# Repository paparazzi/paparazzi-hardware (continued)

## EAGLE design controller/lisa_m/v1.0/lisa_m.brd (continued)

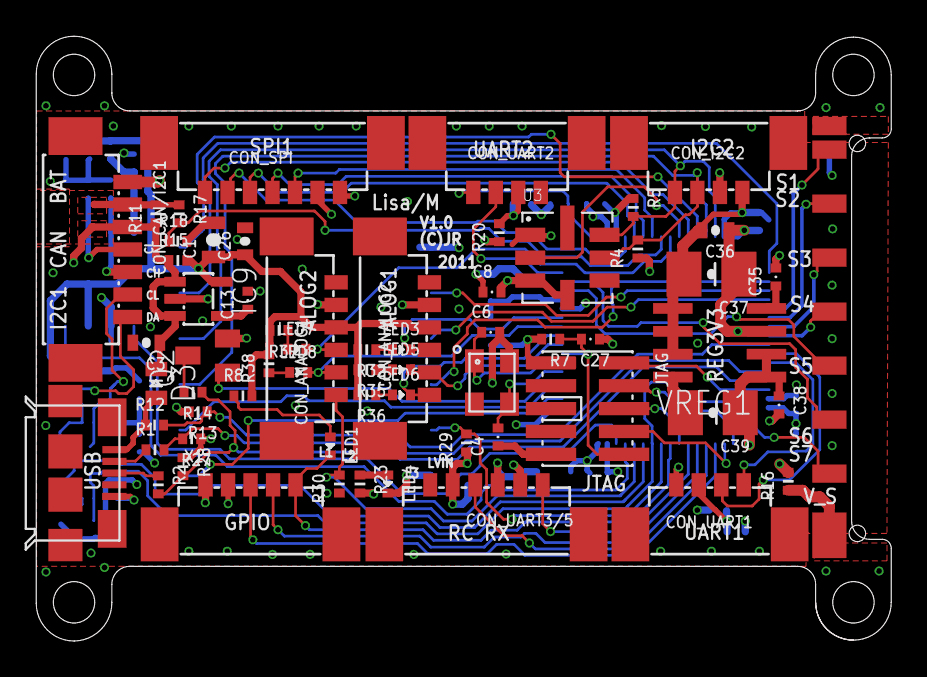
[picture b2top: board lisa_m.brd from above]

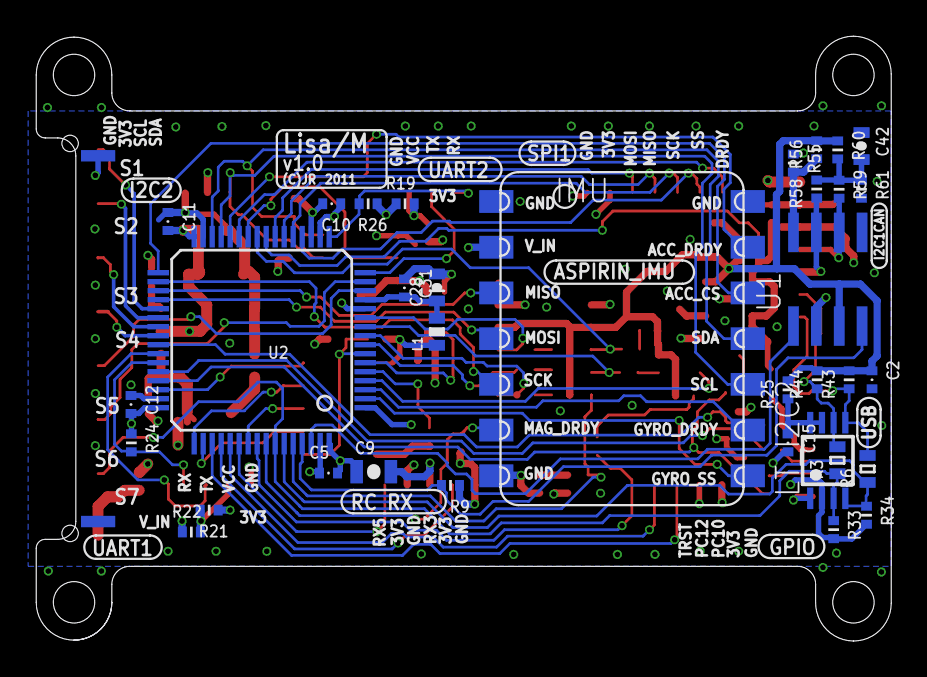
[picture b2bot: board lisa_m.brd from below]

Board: 4 copper layers, 47.5 x 33.6 mm, 97 parts (34 on the bottom side), 82 nets.

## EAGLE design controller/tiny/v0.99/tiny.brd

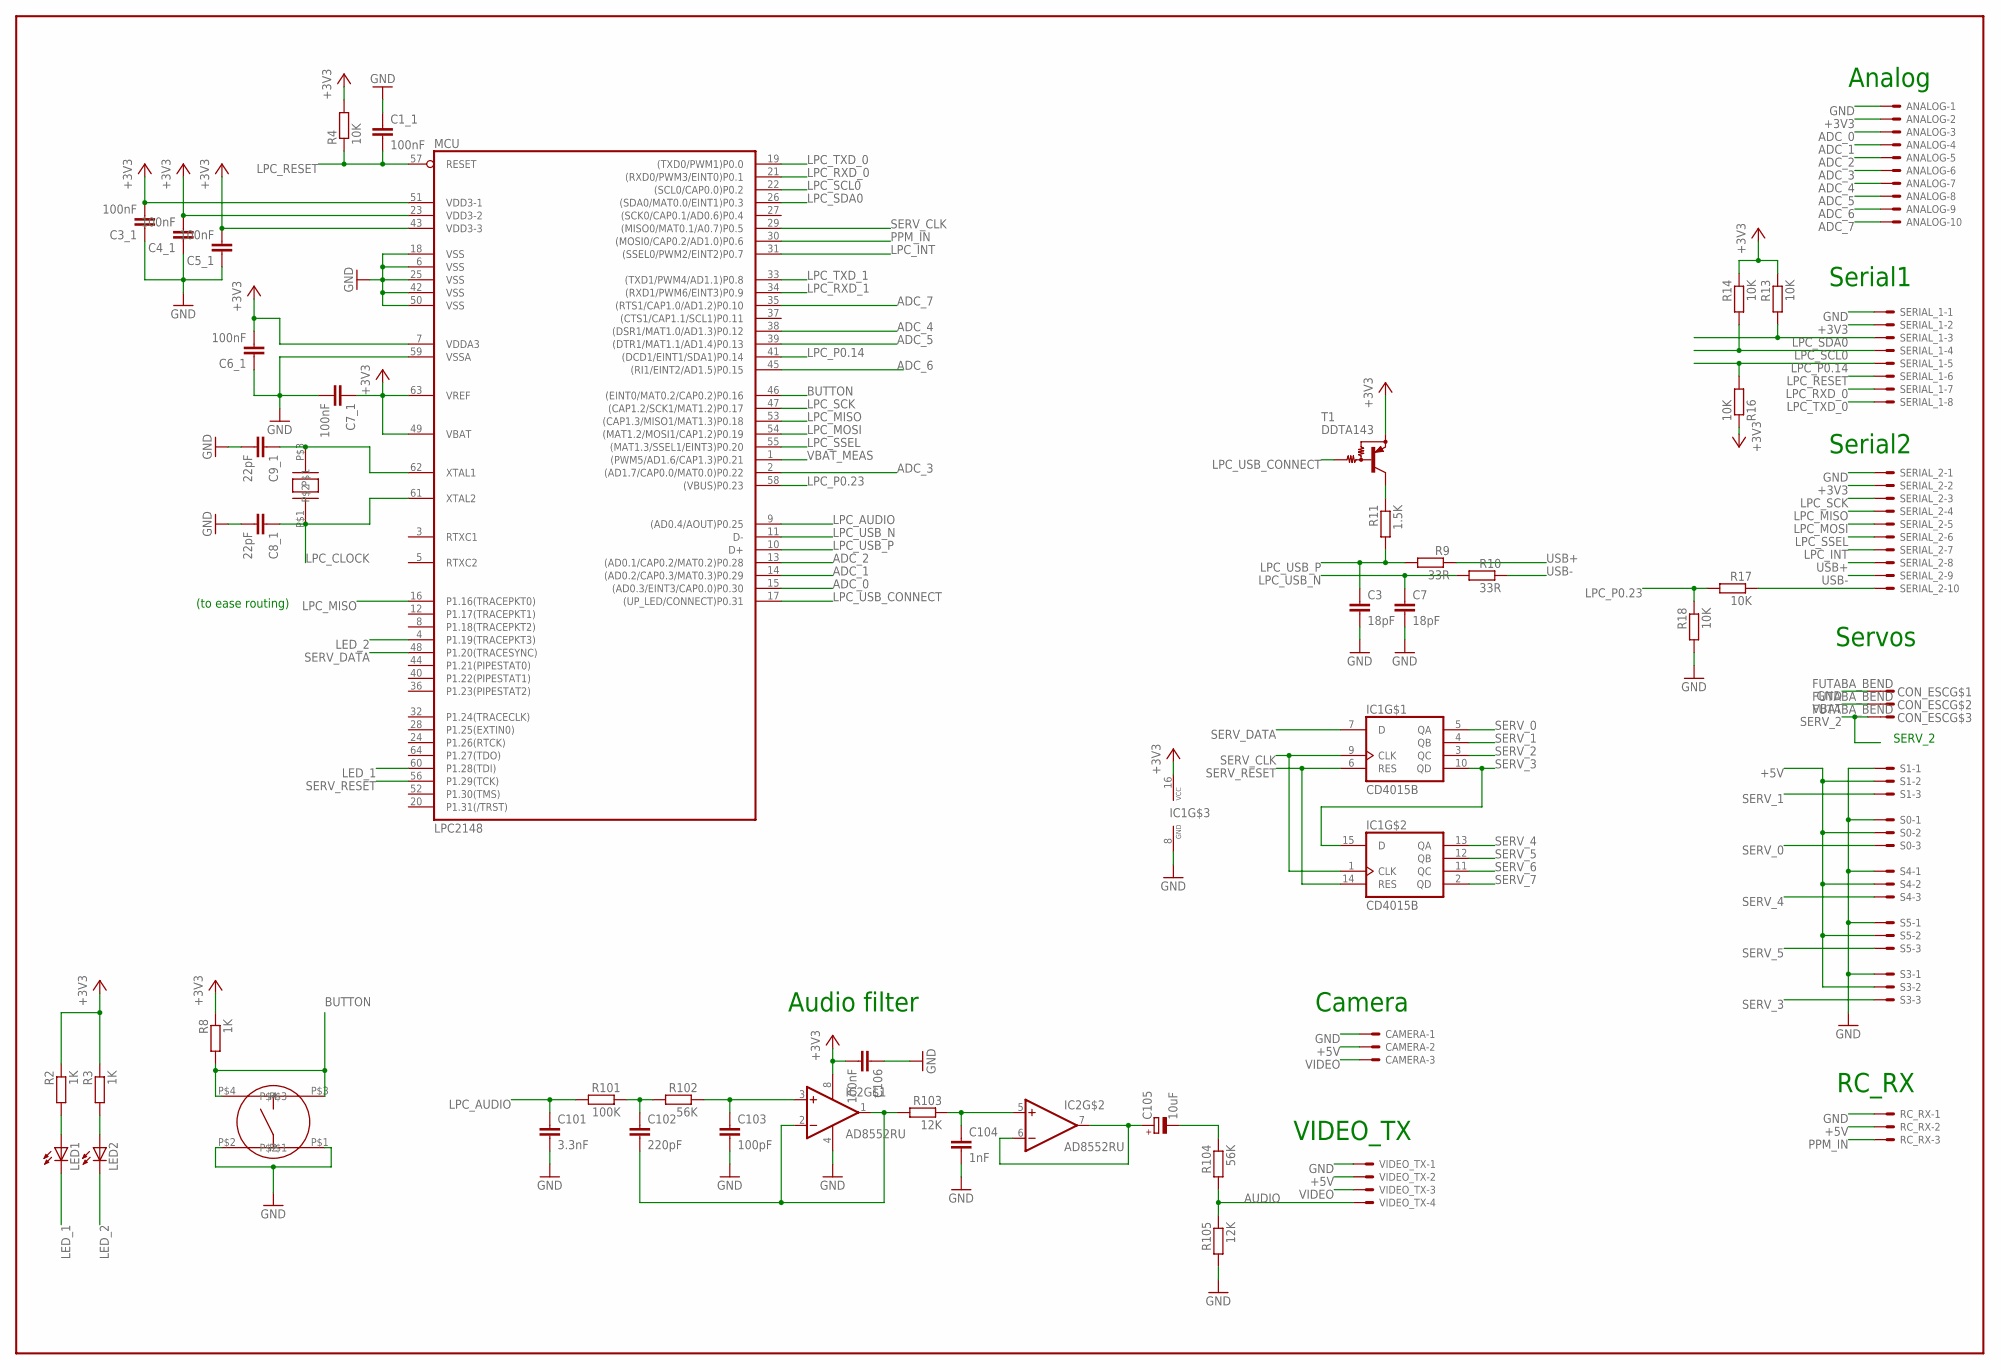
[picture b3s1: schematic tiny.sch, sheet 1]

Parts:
ANALOG: 53047-10
C1_1, C3_1, C4_1, C5_1, C6_1, C7_1, C106: 100nF; C0402K
C3, C7: 18pF; C0402K
C8_1, C9_1: 22pF; C0402K
C101: 3.3nF; C0402K
C102: 220pF; C0402K
C103: 100pF; C0402K
C104: 1nF; C0402K
C105: 10uF; A/3216-18R
CAMERA: 53047-03
CON_ESC: FUTABA_BEND; FUTABA_BENDED
IC1: CD4015B; TSSOP16
IC2: AD8552RU; TSSOP8
LED1, LED2: LEDCHIP-LED0805; CHIP-LED0805
MCU: LPC2148; SQFP-S-10X10-64
Q1: 12MHz; CTS_CRYSTAL
R2, R3, R8: 1K; R1005
R4, R13, R14, R16, R17, R18: 10K; R1005
R9, R10: 33R; R1005
R11: 1.5K; R1005
R101: 100K; R1005
R102, R104: 56K; R1005
R103, R105: 12K; R1005
RC_RX: 53047-03
S0, S1, S3, S4, S5: 53047-03
SERIAL_1: 53047-08
SERIAL_2: 53047-10
SW1: B3S
T1: DDTA143; SC59-BEC
VIDEO_TX: 53047-04

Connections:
+3V3: ANALOG.2, C3_1.2, C4_1.2, C5_1.2, C6_1.2, C7_1.1, C106.2, IC1.16 (VCC), IC2.8 (V+), MCU.7 (VDDA3), MCU.23 (VDD3-2), MCU.43 (VDD3-3), MCU.49 (VBAT), MCU.51 (VDD3-1), MCU.63 (VREF), R2.1, R3.1, R4.2, R8.1, R13.1, R14.1, R16.1, SERIAL_1.2, SERIAL_2.2, T1.E; also elsewhere on the board
+5V: CAMERA.2, RC_RX.2, S0.2, S1.2, S3.2, S4.2, S5.2, VIDEO_TX.2; also elsewhere on the board
ADC_0: ANALOG.3, MCU.15 ((AD0.3/EINT3/CAP0.0)P0.30)
ADC_1: ANALOG.4, MCU.14 ((AD0.2/CAP0.3/MAT0.3)P0.29)
ADC_2: ANALOG.5, MCU.13 ((AD0.1/CAP0.2/MAT0.2)P0.28)
ADC_3: ANALOG.6, MCU.2 ((AD1.7/CAP0.0/MAT0.0)P0.22)
ADC_4: ANALOG.7, MCU.38 ((DSR1/MAT1.0/AD1.3)P0.12)
ADC_5: ANALOG.8, MCU.39 ((DTR1/MAT1.1/AD1.4)P0.13)
ADC_6: ANALOG.9, MCU.45 ((RI1/EINT2/AD1.5)P0.15)
ADC_7: ANALOG.10, MCU.35 ((RTS1/CAP1.0/AD1.2)P0.10)
AUDIO: R104.2, R105.1, VIDEO_TX.4
BUTTON: MCU.46 ((EINT0/MAT0.2/CAP0.2)P0.16), R8.2, SW1.P$3, SW1.P$4
GND: ANALOG.1, C1_1.1, C3.2, C3_1.1, C4_1.1, C5_1.1, C6_1.1, C7.2, C7_1.2, C8_1.2, C9_1.2, C101.2, C103.2, C104.2, C106.1, CAMERA.1, CON_ESC.1, IC1.8 (GND), IC2.4 (V-), MCU.6 (VSS), MCU.18 (VSS), MCU.25 (VSS), MCU.42 (VSS), MCU.50 (VSS), MCU.59 (VSSA), R18.2, R105.2, RC_RX.1, S0.1, S1.1, S3.1, S4.1, S5.1, SERIAL_1.1, SERIAL_2.1, SW1.P$1, SW1.P$2, VIDEO_TX.1; also elsewhere on the board
LED_1: LED1.C, MCU.60 (P1.28(TDI))
LED_2: LED2.C, MCU.4 (P1.19(TRACEPKT3))
LPC_AUDIO: C101.1, MCU.9 ((AD0.4/AOUT)P0.25), R101.2
LPC_CLOCK: C8_1.1, MCU.61 (XTAL2), Q1.P$1
LPC_INT: MCU.31 ((SSEL0/PWM2/EINT2)P0.7), SERIAL_2.7
LPC_MISO: MCU.16 (P1.16(TRACEPKT0)), MCU.53 ((CAP1.3/MISO1/MAT1.3)P0.18), SERIAL_2.4
LPC_MOSI: MCU.54 ((MAT1.2/MOSI1/CAP1.2)P0.19), SERIAL_2.5
LPC_P0.14: MCU.41 ((DCD1/EINT1/SDA1)P0.14), R16.2, SERIAL_1.5
LPC_P0.23: MCU.58 ((VBUS)P0.23), R17.2, R18.1
LPC_RESET: C1_1.2, MCU.57 (RESET), R4.1, SERIAL_1.6
LPC_RXD_0: MCU.21 ((RXD0/PWM3/EINT0)P0.1), SERIAL_1.7
LPC_RXD_1: MCU.34 ((RXD1/PWM6/EINT3)P0.9); also elsewhere on the board
LPC_SCK: MCU.47 ((CAP1.2/SCK1/MAT1.2)P0.17), SERIAL_2.3
LPC_SCL0: MCU.22 ((SCL0/CAP0.0)P0.2), R14.2, SERIAL_1.4
LPC_SDA0: MCU.26 ((SDA0/MAT0.0/EINT1)P0.3), R13.2, SERIAL_1.3
LPC_SSEL: MCU.55 ((MAT1.3/SSEL1/EINT3)P0.20), SERIAL_2.6
LPC_TXD_0: MCU.19 ((TXD0/PWM1)P0.0), SERIAL_1.8
LPC_TXD_1: MCU.33 ((TXD1/PWM4/AD1.1)P0.8); also elsewhere on the board
LPC_USB_CONNECT: MCU.17 ((UP_LED/CONNECT)P0.31), T1.B
LPC_USB_N: C7.1, MCU.11 (D-), R10.2
LPC_USB_P: C3.1, MCU.10 (D+), R9.2, R11.2
unnamed: R17.1, SERIAL_2.10
unnamed: C9_1.1, MCU.62 (XTAL1), Q1.P$3
unnamed: R11.1, T1.C
unnamed: C105.+, IC2.6 (-IN), IC2.7 (OUT)
unnamed: C102.2, IC2.1 (OUT), IC2.2 (-IN), R103.2
unnamed: C102.1, R101.1, R102.2
unnamed: C103.1, IC2.3 (+IN), R102.1
unnamed: C105.-, R104.1
unnamed: C104.1, IC2.5 (+IN), R103.1
unnamed: LED1.A, R2.2
unnamed: LED2.A, R3.2
PPM_IN: MCU.30 ((MOSI0/CAP0.2/AD1.0)P0.6), RC_RX.3
SERV_0: IC1.5 (QA), S0.3
SERV_1: IC1.4 (QB), S1.3
SERV_2: CON_ESC.3, IC1.3 (QC)
SERV_3: IC1.10 (QD), IC1.15 (D), S3.3
SERV_4: IC1.13 (QA), S4.3
SERV_5: IC1.12 (QB), S5.3
SERV_6: IC1.11 (QC)
SERV_7: IC1.2 (QD)
SERV_CLK: IC1.1 (CLK), IC1.9 (CLK), MCU.29 ((MISO0/MAT0.1/A0.7)P0.5)
SERV_DATA: IC1.7 (D), MCU.48 (P1.20(TRACESYNC))
SERV_RESET: IC1.6 (RES), IC1.14 (RES), MCU.56 (P1.29(TCK))
USB+: R9.1, SERIAL_2.8
USB-: R10.1, SERIAL_2.9
VBAT: CON_ESC.2; also elsewhere on the board
VBAT_MEAS: MCU.1 ((PWM5/AD1.6/CAP1.3)P0.21); also elsewhere on the board
VIDEO: CAMERA.3, VIDEO_TX.3

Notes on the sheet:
Servos
Serial2
VIDEO_TX
Analog
Camera
RC_RX
SERV_2
(to ease routing)
Serial1
Audio filter

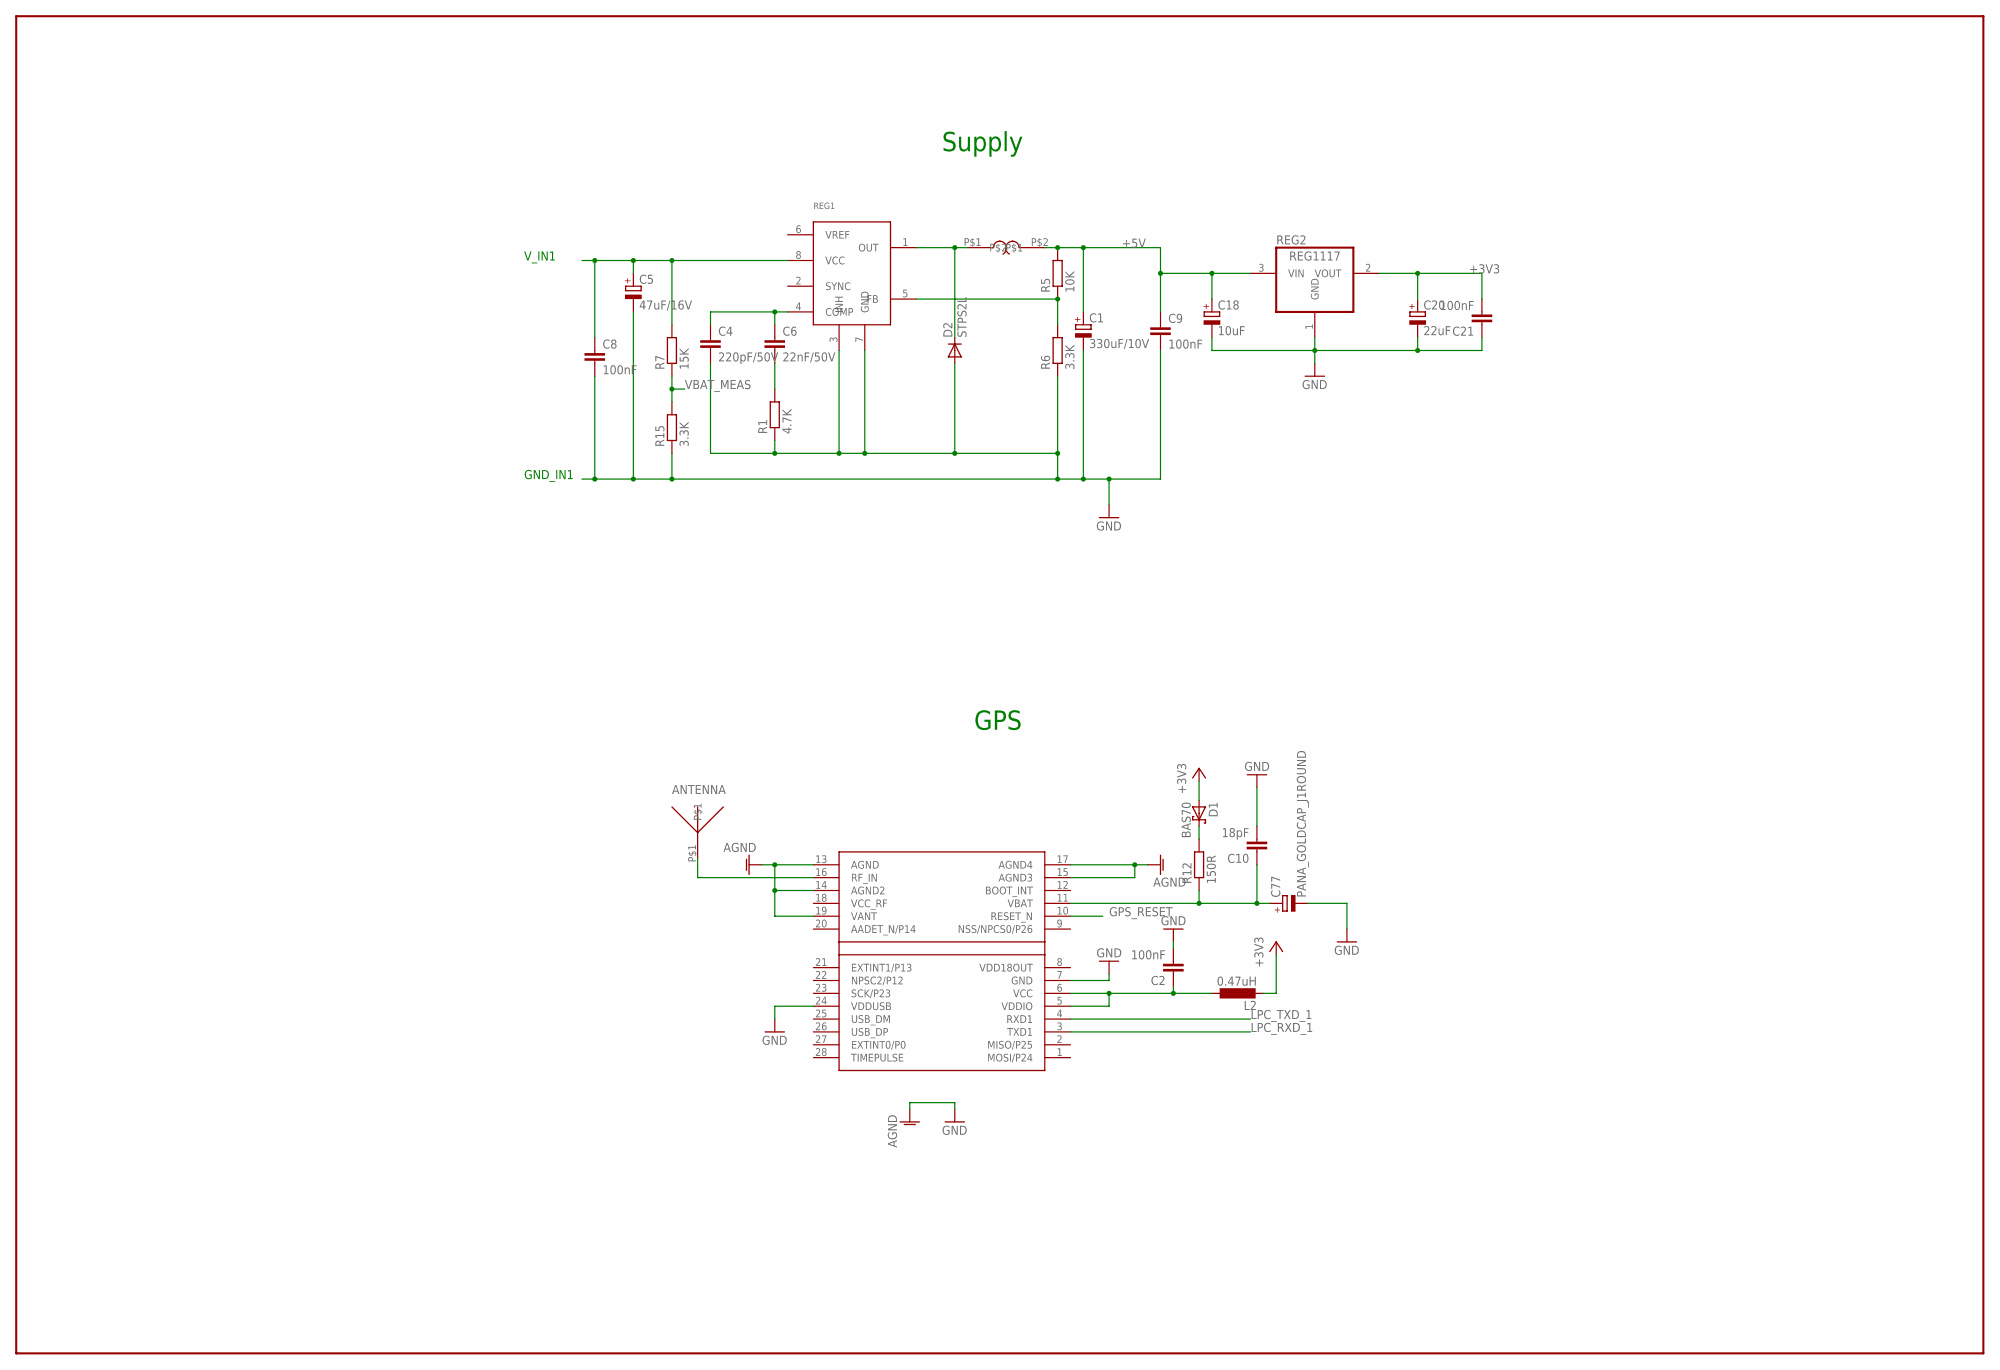
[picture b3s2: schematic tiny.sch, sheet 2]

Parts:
ANTENNA: GPS_ANT_13
C1: 330uF/10V; D/7343-31R
C2: 100nF; C0402K
C4: 220pF/50V; C1206K
C5: 47uF/16V; D/7343-31R
C6: 22nF/50V; C1206K
C8, C9, C21: 100nF; C0603
C10: 18pF; C0402K
C18: 10uF; A/3216-18R
C20: 22uF; B/3528-21R
C77: PANA_GOLDCAP_J1ROUND; PANA_J1_BIS
D1: BAS70; SOT23
D2: STPS2L; SMA
GPS: LEA-4P; LEA-LA
L1: 15uH; WE_PD
L2: 0.47uH; L2012C
R1: 4.7K; R1005
R5: 10K; R1005
R6, R15: 3.3K; R1005
R7: 15K; R1005
R12: 150R; R1005
REG1: L5973D; SO08
REG2: REG1117; SOT223

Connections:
+3V3: C20.+, C21.2, D1.1 (A), L2.2, REG2.2 (VOUT); also elsewhere on the board
+5V: C1.+, C9.1, C18.+, L1.P$2, R5.2, REG2.3 (VIN); also elsewhere on the board
GND: C1.-, C2.2, C4.2, C5.-, C8.2, C9.2, C10.2, C18.-, C20.-, C21.1, C77.MINUS (-), D2.P$1 (A), GPS.7 (GND), GPS.13 (AGND), GPS.14 (AGND2), GPS.15 (AGND3), GPS.17 (AGND4), GPS.19 (VANT), GPS.24 (VDDUSB), R1.1, R6.1, R15.1, REG1.3 (INH), REG1.7 (GND), REG2.1 (GND); also elsewhere on the board
GPS_RESET: GPS.10 (RESET_N)
LPC_RXD_1: GPS.3 (TXD1); also elsewhere on the board
LPC_TXD_1: GPS.4 (RXD1); also elsewhere on the board
unnamed: C2.1, GPS.5 (VDDIO), GPS.6 (VCC), L2.1
unnamed: ANTENNA.P$1, GPS.16 (RF_IN)
unnamed: C4.1, C6.1, REG1.4 (COMP)
unnamed: C6.2, R1.2
unnamed: D2.P$2 (C), L1.P$1, REG1.1 (OUT)
unnamed: R5.1, R6.2, REG1.5 (FB)
unnamed: C10.1, C77.PLUS (+), GPS.11 (VBAT), R12.1
unnamed: D1.3 (C), R12.2
VBAT: C5.+, C8.1, R7.2, REG1.8 (VCC); also elsewhere on the board
VBAT_MEAS: R7.1, R15.2; also elsewhere on the board
VCC_RF: GPS.18 (VCC_RF)
VDD18OUT: GPS.8 (VDD18OUT)

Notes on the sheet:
V_IN1
GND_IN1
Supply
GPS

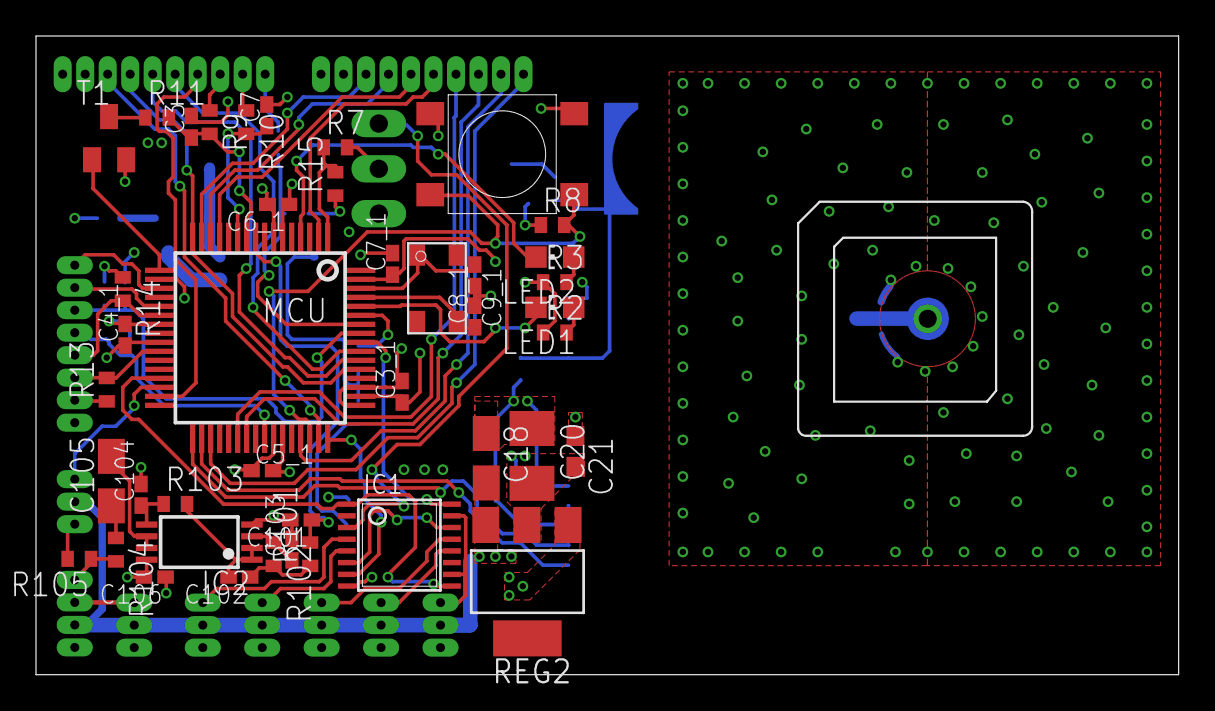
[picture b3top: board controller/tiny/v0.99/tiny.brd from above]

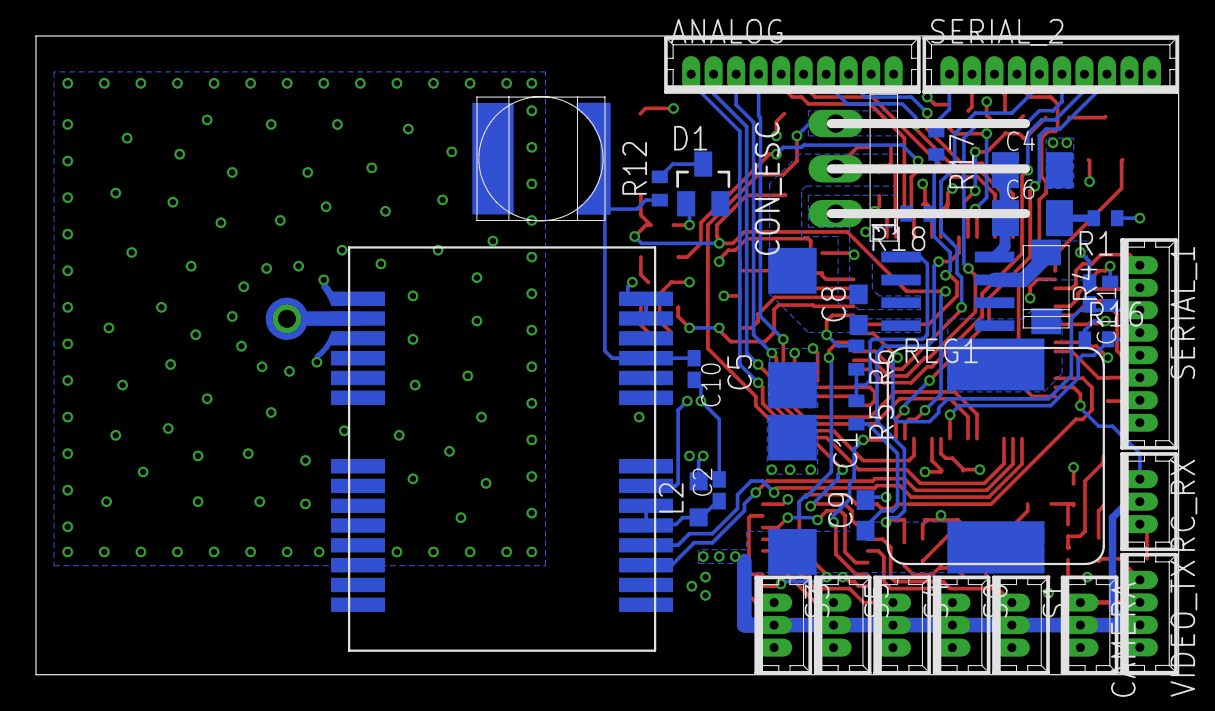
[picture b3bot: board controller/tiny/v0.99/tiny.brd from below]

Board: 4 copper layers, 63.5 x 35.5 mm, 79 parts (36 on the bottom side), 68 nets.

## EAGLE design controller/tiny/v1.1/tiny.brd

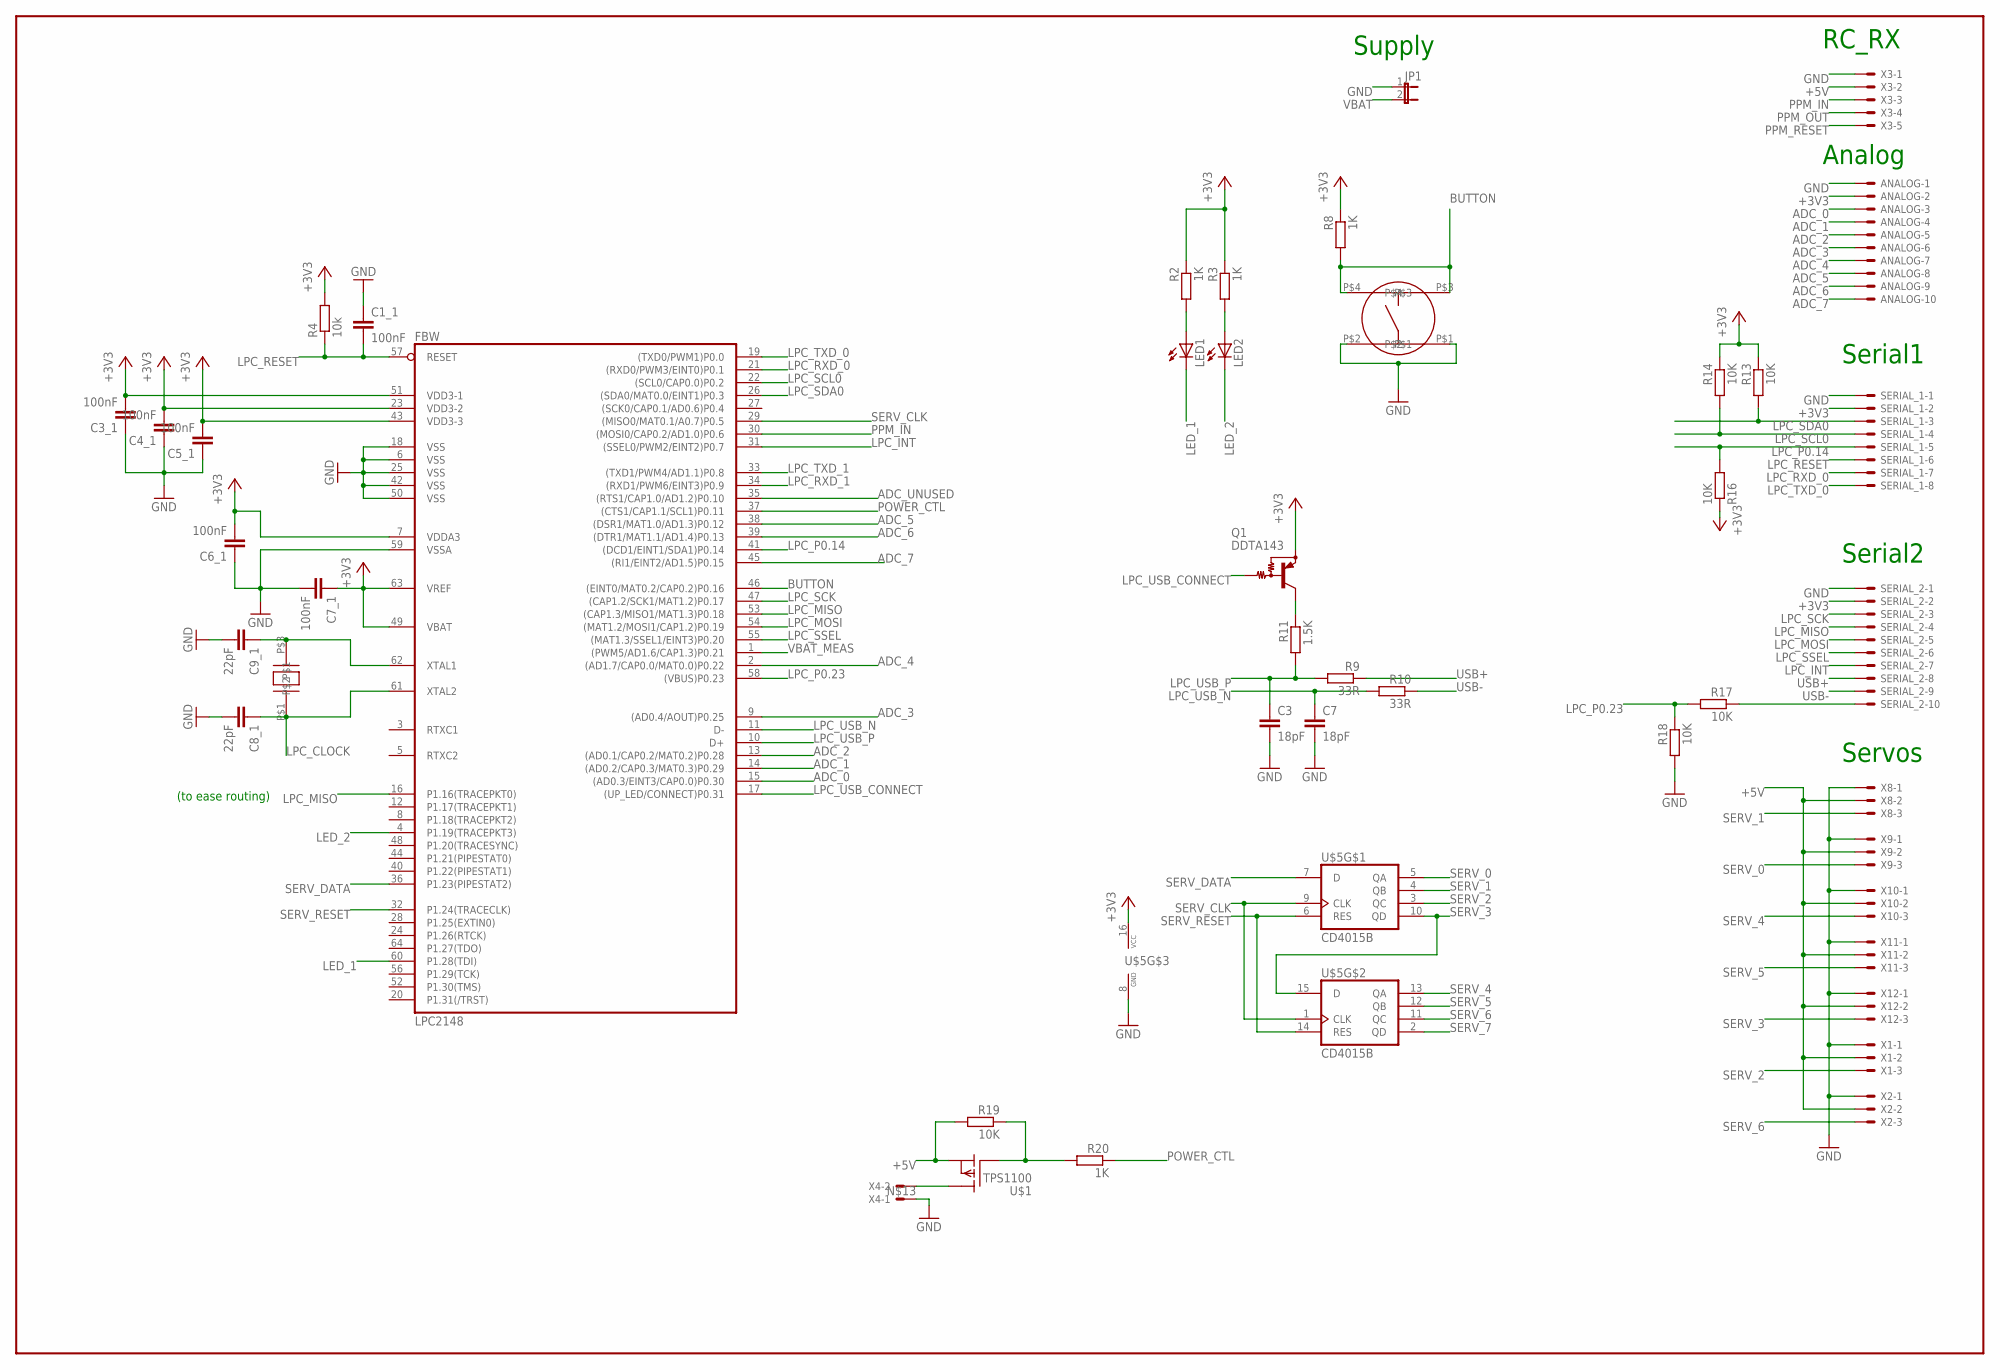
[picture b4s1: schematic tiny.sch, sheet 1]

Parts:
ANALOG: 53047-10
C1_1, C3_1, C4_1, C5_1, C6_1, C7_1: 100nF; C0402K
C3, C7: 18pF; C0402K
C8_1, C9_1: 22pF; C0402K
FBW: LPC2148; SQFP-S-10X10-64
JP1: JP1E; JP1
LED1, LED2: LEDCHIP-LED0805; CHIP-LED0805
Q1: DDTA143; SC59-BEC
R2, R3, R8, R20: 1K; R1005
R4: 10k; R1005
R9, R10: 33R; R1005
R11: 1.5K; R1005
R13, R14, R16, R17, R18, R19: 10K; R1005
SERIAL_1: 53047-08
SERIAL_2: 53047-10
SW1: B3S
U$1: TPS1100; SOIC8
U$5: CD4015B; TSSOP16
U$19: CRYSTAL_CTS; CTS_CRYSTAL
X1, X2, X8, X9, X10, X11, X12: 53047-03
X3: 53047-05
X4: 53047-02

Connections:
+3V3: ANALOG.2, C3_1.2, C4_1.2, C5_1.2, C6_1.2, C7_1.1, FBW.7 (VDDA3), FBW.23 (VDD3-2), FBW.43 (VDD3-3), FBW.49 (VBAT), FBW.51 (VDD3-1), FBW.63 (VREF), Q1.E, R2.1, R3.1, R4.2, R8.1, R13.1, R14.1, R16.1, SERIAL_1.2, SERIAL_2.2, U$5.16 (VCC); also elsewhere on the board
+5V: R19.2, U$1.1 (S), X1.2, X2.2, X3.2, X8.2, X9.2, X10.2, X11.2, X12.2; also elsewhere on the board
ADC_0: ANALOG.3, FBW.15 ((AD0.3/EINT3/CAP0.0)P0.30)
ADC_1: ANALOG.4, FBW.14 ((AD0.2/CAP0.3/MAT0.3)P0.29)
ADC_2: ANALOG.5, FBW.13 ((AD0.1/CAP0.2/MAT0.2)P0.28)
ADC_3: ANALOG.6, FBW.9 ((AD0.4/AOUT)P0.25)
ADC_4: ANALOG.7, FBW.2 ((AD1.7/CAP0.0/MAT0.0)P0.22)
ADC_5: ANALOG.8, FBW.38 ((DSR1/MAT1.0/AD1.3)P0.12)
ADC_6: ANALOG.9, FBW.39 ((DTR1/MAT1.1/AD1.4)P0.13)
ADC_7: ANALOG.10, FBW.45 ((RI1/EINT2/AD1.5)P0.15)
ADC_UNUSED: FBW.35 ((RTS1/CAP1.0/AD1.2)P0.10)
BUTTON: FBW.46 ((EINT0/MAT0.2/CAP0.2)P0.16), R8.2, SW1.P$3, SW1.P$4
GND: ANALOG.1, C1_1.1, C3.2, C3_1.1, C4_1.1, C5_1.1, C6_1.1, C7.2, C7_1.2, C8_1.2, C9_1.2, FBW.6 (VSS), FBW.18 (VSS), FBW.25 (VSS), FBW.42 (VSS), FBW.50 (VSS), FBW.59 (VSSA), JP1.1, R18.2, SERIAL_1.1, SERIAL_2.1, SW1.P$1, SW1.P$2, U$5.8 (GND), X1.1, X2.1, X3.1, X4.1, X8.1, X9.1, X10.1, X11.1, X12.1; also elsewhere on the board
LED_1: FBW.60 (P1.28(TDI)), LED1.C
LED_2: FBW.4 (P1.19(TRACEPKT3)), LED2.C
LPC_CLOCK: C8_1.1, FBW.61 (XTAL2), U$19.P$1
LPC_INT: FBW.31 ((SSEL0/PWM2/EINT2)P0.7), SERIAL_2.7
LPC_MISO: FBW.16 (P1.16(TRACEPKT0)), FBW.53 ((CAP1.3/MISO1/MAT1.3)P0.18), SERIAL_2.4
LPC_MOSI: FBW.54 ((MAT1.2/MOSI1/CAP1.2)P0.19), SERIAL_2.5
LPC_P0.14: FBW.41 ((DCD1/EINT1/SDA1)P0.14), R16.2, SERIAL_1.5
LPC_P0.23: FBW.58 ((VBUS)P0.23), R17.2, R18.1
LPC_RESET: C1_1.2, FBW.57 (RESET), R4.1, SERIAL_1.6
LPC_RXD_0: FBW.21 ((RXD0/PWM3/EINT0)P0.1), SERIAL_1.7
LPC_RXD_1: FBW.34 ((RXD1/PWM6/EINT3)P0.9); also elsewhere on the board
LPC_SCK: FBW.47 ((CAP1.2/SCK1/MAT1.2)P0.17), SERIAL_2.3
LPC_SCL0: FBW.22 ((SCL0/CAP0.0)P0.2), R14.2, SERIAL_1.4
LPC_SDA0: FBW.26 ((SDA0/MAT0.0/EINT1)P0.3), R13.2, SERIAL_1.3
LPC_SSEL: FBW.55 ((MAT1.3/SSEL1/EINT3)P0.20), SERIAL_2.6
LPC_TXD_0: FBW.19 ((TXD0/PWM1)P0.0), SERIAL_1.8
LPC_TXD_1: FBW.33 ((TXD1/PWM4/AD1.1)P0.8); also elsewhere on the board
LPC_USB_CONNECT: FBW.17 ((UP_LED/CONNECT)P0.31), Q1.B
LPC_USB_N: C7.1, FBW.11 (D-), R10.2
LPC_USB_P: C3.1, FBW.10 (D+), R9.2, R11.2
unnamed: R17.1, SERIAL_2.10
unnamed: C9_1.1, FBW.62 (XTAL1), U$19.P$3
unnamed: Q1.C, R11.1
unnamed: R19.1, R20.2, U$1.4 (G)
unnamed: U$1.5 (D), X4.2
unnamed: LED1.A, R2.2
unnamed: LED2.A, R3.2
POWER_CTL: FBW.37 ((CTS1/CAP1.1/SCL1)P0.11), R20.1
PPM_IN: FBW.30 ((MOSI0/CAP0.2/AD1.0)P0.6), X3.3
PPM_OUT: X3.4
PPM_RESET: X3.5
SERV_0: U$5.5 (QA), X9.3
SERV_1: U$5.4 (QB), X8.3
SERV_2: U$5.3 (QC), X1.3
SERV_3: U$5.10 (QD), U$5.15 (D), X12.3
SERV_4: U$5.13 (QA), X10.3
SERV_5: U$5.12 (QB), X11.3
SERV_6: U$5.11 (QC), X2.3
SERV_7: U$5.2 (QD)
SERV_CLK: FBW.29 ((MISO0/MAT0.1/A0.7)P0.5), U$5.1 (CLK), U$5.9 (CLK)
SERV_DATA: FBW.36 (P1.23(PIPESTAT2)), U$5.7 (D)
SERV_RESET: FBW.32 (P1.24(TRACECLK)), U$5.6 (RES), U$5.14 (RES)
USB+: R9.1, SERIAL_2.8
USB-: R10.1, SERIAL_2.9
VBAT: JP1.2; also elsewhere on the board
VBAT_MEAS: FBW.1 ((PWM5/AD1.6/CAP1.3)P0.21); also elsewhere on the board

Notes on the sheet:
Servos
Serial1
Analog
RC_RX
(to ease routing)
Serial2
Supply

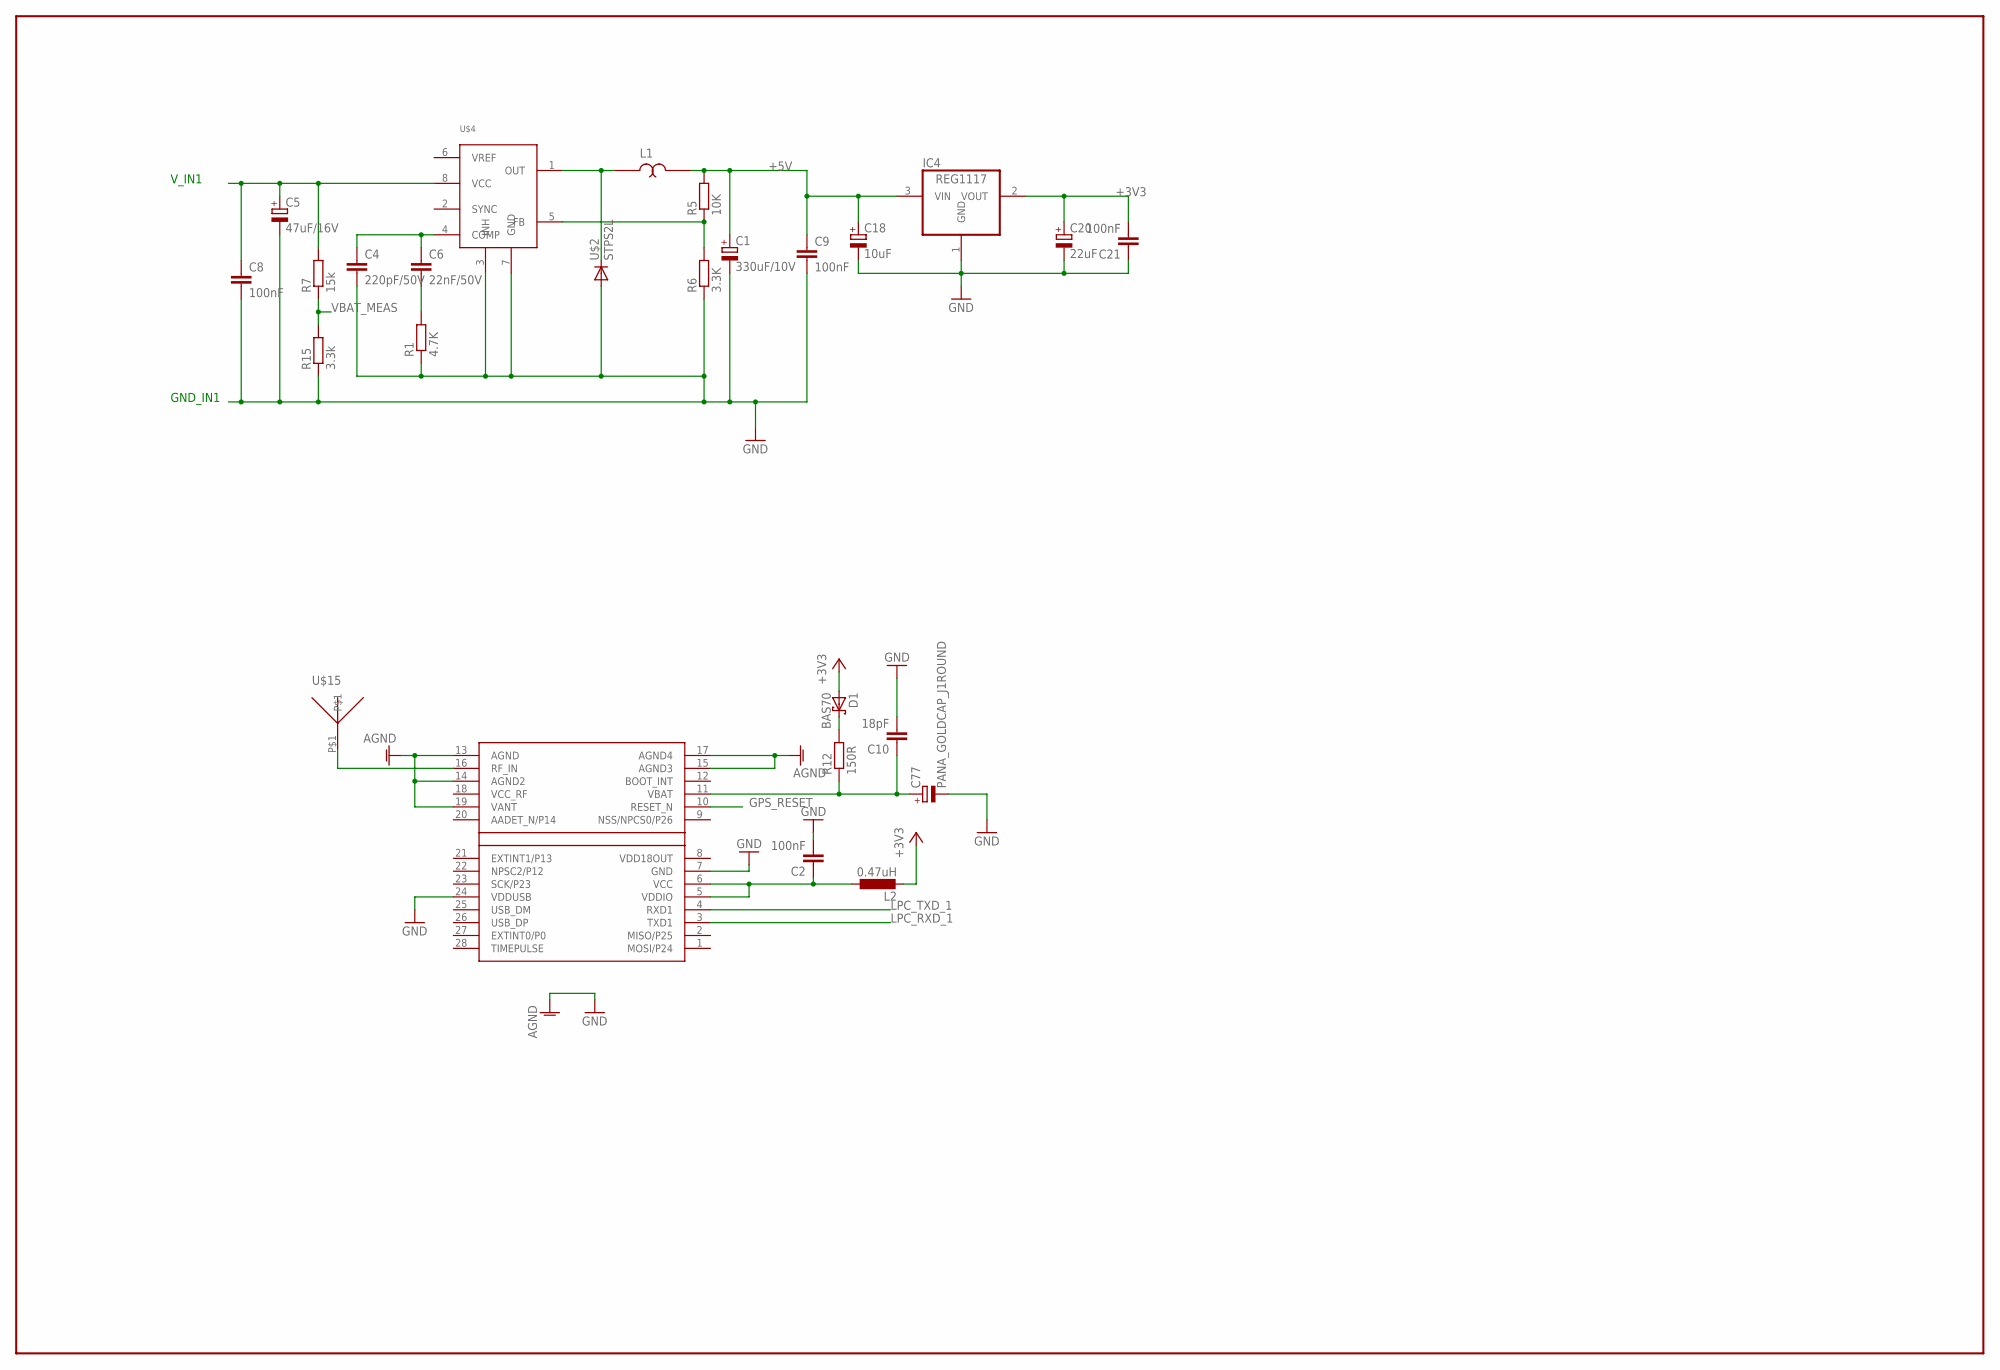
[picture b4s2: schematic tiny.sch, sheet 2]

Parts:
C1: 330uF/10V; D/7343-31R
C2: 100nF; C0402K
C4: 220pF/50V; C1206K
C5: 47uF/16V; D/7343-31R
C6: 22nF/50V; C1206K
C8, C9, C21: 100nF; C0603
C10: 18pF; C0402K
C18: 10uF; A/3216-18R
C20: 22uF; B/3528-21R
C77: PANA_GOLDCAP_J1ROUND; PANA_J1_BIS
D1: BAS70; SOT23
IC4: REG1117; SOT223
L1: 15uH; WE_PD
L2: 0.47uH; L2012C
R1: 4.7K; R1005
R5: 10K; R1005
R6: 3.3K; R1005
R7: 15k; R1005
R12: 150R; R1005
R15: 3.3k; R1005
U$2: STPS2L; SMA
U$4: L5973D; SO08
U$6: LEA-4P; LEA-LA
U$15: GPS_ANT_13

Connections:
+3V3: C20.+, C21.2, D1.1 (A), IC4.2 (VOUT), L2.2; also elsewhere on the board
+5V: C1.+, C9.1, C18.+, IC4.3 (VIN), L1.P$2, R5.2; also elsewhere on the board
GND: C1.-, C2.2, C4.2, C5.-, C8.2, C9.2, C10.2, C18.-, C20.-, C21.1, C77.MINUS (-), IC4.1 (GND), R1.1, R6.1, R15.1, U$2.P$1 (A), U$4.3 (INH), U$4.7 (GND), U$6.7 (GND), U$6.13 (AGND), U$6.14 (AGND2), U$6.15 (AGND3), U$6.17 (AGND4), U$6.19 (VANT), U$6.24 (VDDUSB); also elsewhere on the board
GPS_RESET: U$6.10 (RESET_N)
LPC_RXD_1: U$6.3 (TXD1); also elsewhere on the board
LPC_TXD_1: U$6.4 (RXD1); also elsewhere on the board
unnamed: C2.1, L2.1, U$6.5 (VDDIO), U$6.6 (VCC)
unnamed: U$6.16 (RF_IN), U$15.P$1
unnamed: C4.1, C6.1, U$4.4 (COMP)
unnamed: C6.2, R1.2
unnamed: L1.P$1, U$2.P$2 (C), U$4.1 (OUT)
unnamed: R5.1, R6.2, U$4.5 (FB)
unnamed: C10.1, C77.PLUS (+), R12.1, U$6.11 (VBAT)
unnamed: D1.3 (C), R12.2
VBAT: C5.+, C8.1, R7.2, U$4.8 (VCC); also elsewhere on the board
VBAT_MEAS: R7.1, R15.2; also elsewhere on the board
VCC_RF: U$6.18 (VCC_RF)
VDD18OUT: U$6.8 (VDD18OUT)

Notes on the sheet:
V_IN1
GND_IN1

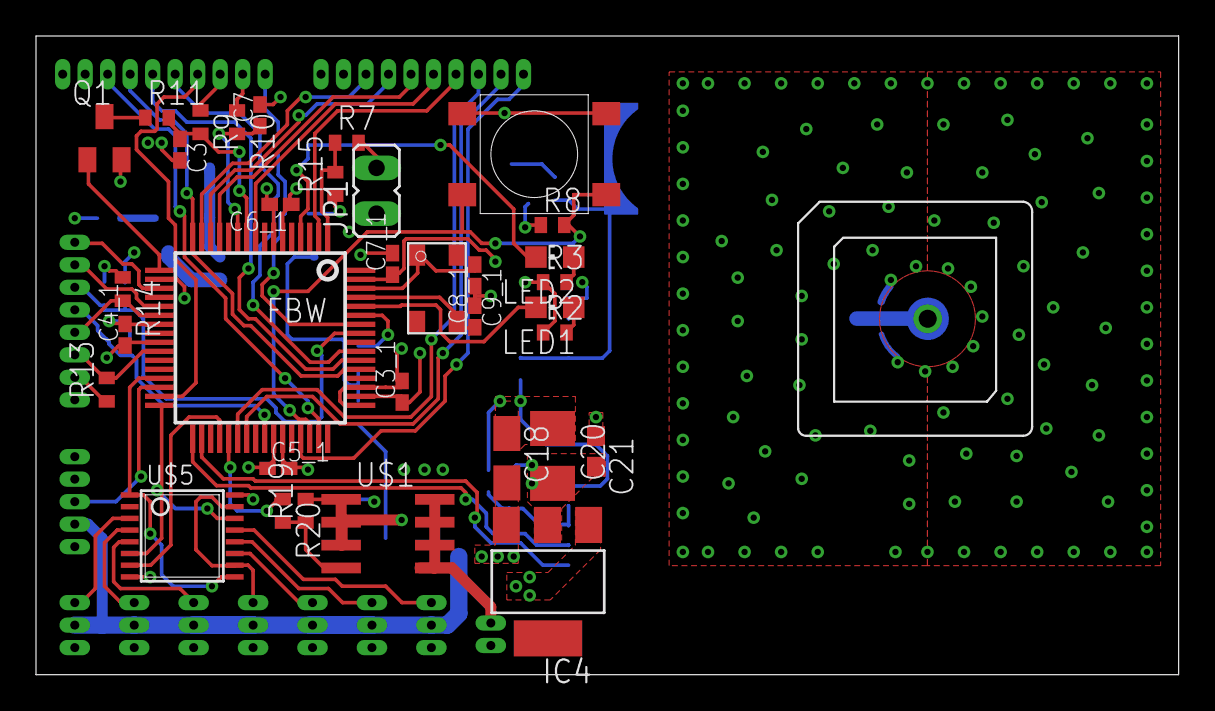
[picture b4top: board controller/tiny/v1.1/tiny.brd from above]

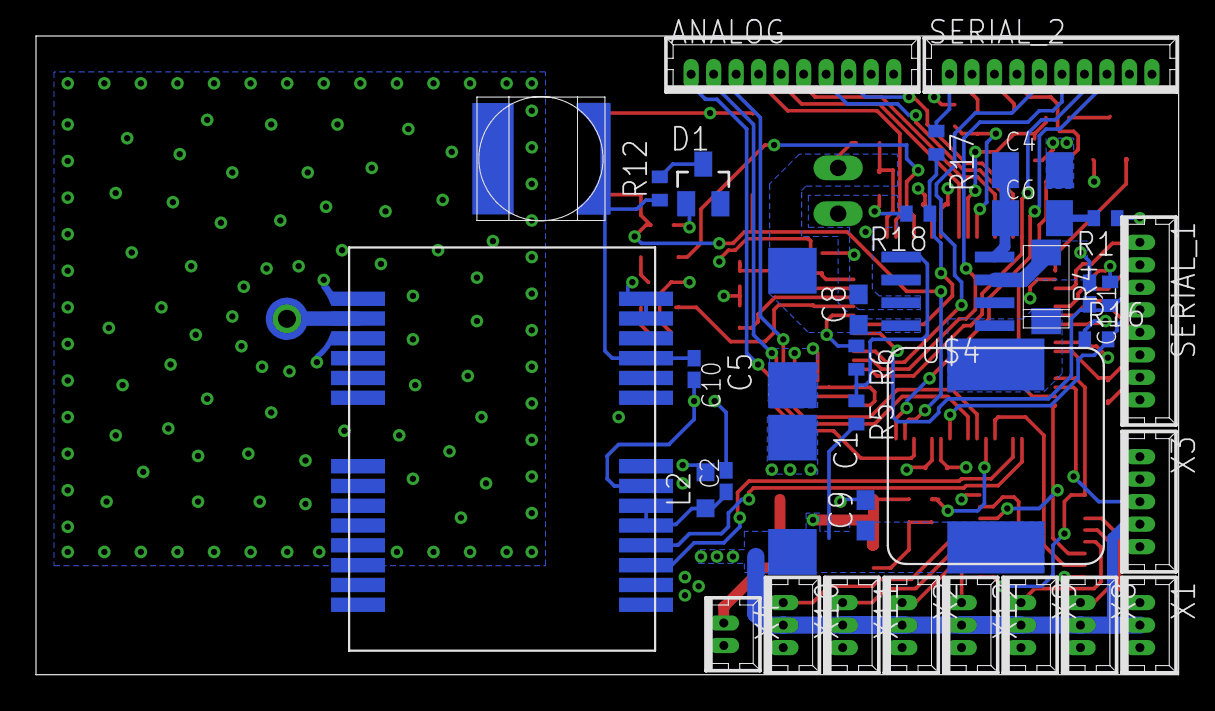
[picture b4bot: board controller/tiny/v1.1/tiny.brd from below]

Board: 4 copper layers, 63.5 x 35.5 mm, 71 parts (36 on the bottom side), 63 nets.
